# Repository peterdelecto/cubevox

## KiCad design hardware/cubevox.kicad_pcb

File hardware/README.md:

# cubevox hardware

KiCad scaffold cloned from Teensy-H7-Port (read-only source, fxbox commit 48f1e82,
`hardware/fxbox` + `hardware/h7core`). The schematic (`cubevox.kicad_sch` plus the
`h7core_block` child sheet) and the PCB (`cubevox.kicad_pcb`) exist; revision 2 follows
`docs/audits/2026-10-02-schematic-audit.md` (disposition in `...-schematic-audit-response.md`).
Audits, consult packets and reviews all live in `docs/audits/`, dated. The 2026-10-08 order
(a41fe4b) was held for the power switch SWPWR1 and J101 at x 175 (owner 2026-10-09);
`tools/gates.sh` checks the layout, `RUNLOG.md` is the record.

## Contents
1. `cubevox.kicad_sym`, `cubevox.pretty`, `cubevox.3dshapes` - JLC parts from fxbox (20 symbols).
2. `cubevox_h7core.*` - same three for the h7core block (25 symbols, MCU, power, codecs).
3. `sym-lib-table`, `fp-lib-table` - both libs, `${KIPRJMOD}`-relative.
4. `cubevox.json`, `h7core_block.json` - `foreman schematic` specs generated by
   `tools/build_spec.py` from the fxbox sources in `tools/src/`. Edit the generator, not the JSON.
5. `reference/` - fxbox schematics, unmodified, not the cubevox schematic.

## Recipe order (docs/specs/2026-10-02-hardware-design.md)
purpose line, `foreman brief`, PARTS.md with LCSC codes, `foreman schematic` from the
JSON spec, ERC 0 plus visual render, layout. Run `assign_pin_types.py` after any import.

## Tooling
kicad-cli 10.0.5 (/Applications/KiCad/KiCad.app).
Source had no tools/build_spec.py; fxbox.json is hand-kept (fxbox/tools has only routing scripts).
Not copied: .kicad_pcb, .kicad_pro, layout/, jlc_extra/ (holds one SMD tact switch).

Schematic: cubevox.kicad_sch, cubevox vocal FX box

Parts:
C101, C113, C116, C118, C127, C130, C134, C143, C144, C145, C150, C151, C152, C153, C154, C155, C156, C157, C162, C163: 100nF; C0603; LCSC C14663
C111: 2.2uF; C0603; LCSC C23630
C112, C114, C115: 22uF; C1206; LCSC C12891
C117, C135, C137, C138: 10uF; C1206; LCSC C14860
C119, C123: 100pF; C0603; LCSC C14858
C120, C124: 47uF 25V; CAP-SMD_BD6.3-L6.6-W6.6-LS7.6-FD; MPN RVT1E470M0605; LCSC C72521
C121, C125, C139, C141, C160: 10uF 25V; CAP-SMD_BD4.0-L4.3-W4.3-FD; MPN RVT1E100M0405; LCSC C72484
C128, C129, C132: 47pF; C0603; LCSC C1671
C136, C161: 2.2nF; C0603; LCSC C2991172
C142: 10nF; C0603; LCSC C57112
C158: 22uF 25V NP; CAP-SMD_BD6.3-L6.6-W6.6-FD; MPN EEEHP1E220P; LCSC C413679
C159: 100uF 10V; CAP-SMD_BD5.0-L5.3-W5.3-LS6.3-FD; MPN VT1A101M0505; LCSC C191859
C167: 100nF; C_0402_1005Metric; LCSC C1525
C168, C169: 10uF; C_0805_2012Metric; LCSC C15850
D105: SMBJ20CA; SMB_L4.4-W3.6-LS5.4-BI; MPN SMBJ20CA; LCSC C113992
D106: SS34; SMA_L4.3-W2.6-LS5.2-RD; MPN SS34; LCSC C8678
D107, D108: BAT54S; SOT-23_L2.9-W1.3-P1.90-LS2.4-BR; MPN BAT54SLT1G; LCSC C19726
D109, D110: 1N4148W; SOD-123F_L2.7-W1.6-LS3.8-RD; MPN 1N4148W; LCSC C81598
ENC101: EC11E15244B2; SW-TH_EC11E; MPN EC11E15244B2; LCSC C470754
FB101: 120R@100MHz; L_0603_1608Metric; MPN BLM18PG121SN1D; LCSC C14709
FB102: 120R@100MHz; L_0603_1608Metric; LCSC C14709
H101, H102, H103, H104: M3 shell; MountingHole_3.2mm_M3
J101: J_IN NCJ6FA-H; CONN-TH_NCJ6FA-H; MPN NCJ6FA-H; LCSC C368458
J106: DC 9V; DC-IN-TH_PJ-002A; MPN PJ-002A; LCSC C3096082
J108: OUT 6.35mm; AUDIO-TH_PJ-611E_1; MPN PJ-611E; LCSC C309282
J117: OLED SH1106; OLED-1.3-SH1106-I2C-4P; MPN SH1106 1.3in I2C 128x64; LCSC C42379197
K102, K103: G6K-2F-Y DC5; RELAY-SMD_G6K-2F-X-XX; MPN G6K-2F-Y-TR DC5; LCSC C47190
L101: 4.7uH; IND-SMD_L5.0-W5.0_ANR5040T; MPN ANR5040T4R7M; LCSC C7427135
Q101, Q102: MMBT3904; SOT-23-3_L2.9-W1.3-P1.90-LS2.4-BR; MPN MMBT3904; LCSC C20526
R101, R104: 47R; R0603; LCSC C23182
R102, R105: 22k; R0603; LCSC C31850
R103, R106: 1.2k; R0603; LCSC C22765
R108, R110: 4.53k; R0603; LCSC C25971
R109, R126, R150, R159, R160: 1k; R0603; LCSC C21190
R111, R112, R113, R114: 10k 0.1%; R0603; MPN ARG03BTC1002; LCSC C309083
R116, R147: 470R; R0603; LCSC C23179
R117, R118, R120, R122, R127, R128, R129, R134, R135, R136, R137, R138, R139, R140, R141, R151, R152: 10k; R0603; LCSC C25804
R119, R124: 100R; R0603; LCSC C22775
R123: 15k; R0603; LCSC C22809
R125, R144, R145, R148, R149, R153, R161: 100k; R0603; LCSC C25803
R142, R143: 4.7k; R0603; LCSC C23162
R146: 22R; R0603; LCSC C23345
R154, R155: 10k; R_0402_1005Metric; LCSC C25744
R162: 100k; R_0402_1005Metric; LCSC C25741
RV101, RV102, RV103, RV104, RV105, RV106, RV107, RV108, RV109, RV110, RV111, RV112, RV113, RV114, RV115, RV116: 10k; RES-ADJ-TH_RK09D1130C2P; MPN RK09D1130C2P; LCSC C361173
RVGAIN1: 10k GAIN; RES-ADJ-TH_RK09D1130C2P; MPN RK09D1130C2P; LCSC C361173
SW101, SW102, SW103, SW104, SW105, SW106, SW107, SW108: ST-0-102 bat toggle; SW-TH_3P-L8.3-W5.2-P2.54_ST-0-102-A01-T000; MPN ST-0-102-A01-T000-LF; LCSC C1788487
SWBYPASS1: ST-0-102 bat toggle; SW-TH_3P-L8.3-W5.2-P2.54_ST-0-102-A01-T000; MPN ST-0-102-A01-T000-LF; LCSC C1788487
SWPWR1: SS-12D11-G050 power; SW-TH_5P-P4.70_SS-12D11-G050; MPN SS-12D11-G050; LCSC C17179528
TP1: 9V_JACK; TestPoint_Pad_D1.5mm
TP2: VIN_9V; TestPoint_Pad_D1.5mm
TP3: GND; TestPoint_Pad_D1.5mm
TP4: 3V3; TestPoint_Pad_D1.5mm
TP6: 3V3A; TestPoint_Pad_D1.5mm
TP7: 5V; TestPoint_Pad_D1.5mm
TP8: 5VA; TestPoint_Pad_D1.5mm
TP9: 5VA_W; TestPoint_Pad_D1.5mm
TP10: VREF_BUF; TestPoint_Pad_D1.5mm
U101: CD74HC4067; SSOP-24_L8.1-W5.3-P0.65-LS7.8-BL; MPN CD74HC4067SM96; LCSC C98457
U103: AP63205WU-7; TSOT-23-6_L2.9-W1.6-P0.95-LS2.8-BL; MPN AP63205WU-7; LCSC C2071056
U104, U105, U106: OPA2197IDR; SOIC-8_L4.9-W3.9-P1.27-LS6.0-BL; MPN OPA2197IDR; LCSC C139363
U108: OPA197IDBVR; SOT-23-5_L3.0-W1.7-P0.95-LS2.8-BR; LCSC C221351

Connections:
/3V3: J117.2 (VCC), R120.1, R127.1, R128.1, R129.1, R134.1, R135.1, R136.1, R137.1, R138.1, R139.1, R140.1, R141.1, R142.1, R143.1, TP4.1 (1_1); also elsewhere on the board
/3V3A: C101.1, C111.1, RV101.3, RV102.3, RV103.3, RV104.3, RV105.3, RV106.3, RV107.3, RV108.3, RV109.3, RV110.3, RV111.3, RV112.3, RV113.3, RV114.3, RV115.3, RV116.3, TP6.1 (1_1), U101.24 (VCC); also elsewhere on the board
/5V: C114.1, C115.1, D109.1 (K), D110.1 (K), FB101.1, FB102.1, K102.1, K103.1, L101.2, TP7.1 (1_1), U103.1 (FB); also elsewhere on the board
/5VA: C117.1, C118.1, C127.1, C134.1, C167.1, D107.2 (C), D108.2 (C), FB101.2, R117.1, R151.1, TP8.1 (1_1), U104.8 (+VS), U105.8 (+VS), U108.5 (V+); also elsewhere on the board
/5VA_W: C130.1, C168.1, FB102.2, R154.1, TP9.1 (1_1), U106.8 (+VS)
/9V_JACK: D106.2 (A), SWPWR1.1, TP1.1 (1_1)
/9V_PLUG: J106.2, J106.3, SWPWR1.2
/A1_FB: C128.2, C158.1, R108.2, U104.2 (-IN/A)
/A2_FB: C129.2, R109.2, R110.2, U104.6 (-IN/B)
/ADC_RC: C136.1, C137.1, R119.2
/ADC_VINL: C137.2; also elsewhere on the board
/ADC_VINR: C138.1; also elsewhere on the board
/BIAS_W: C169.1, R123.2, R154.2, R155.1, U106.3 (+IN/A)
/BUCK5_BST: C116.1, U103.6 (BST)
/BUCK5_SW: C116.2, L101.1, U103.5 (SW)
/BUF_IN: R122.2, R123.1, U106.5 (+IN/B)
/BUF_OUT: R124.1, U106.6 (-IN/B), U106.7 (OUT/B)
/BUF_R: C141.1, R124.2
/DAC_AC: C139.1, R122.1
/DAC_LP: C139.2, C161.1, R147.2
/DAC_OUTL: R147.1; also elsewhere on the board
/DA_N: R113.2, R114.1, U105.2 (-IN/A)
/DA_P: R111.2, R112.1, U105.3 (+IN/A)
/ENC_MENU_A: C143.1, ENC101.A, R127.2; also elsewhere on the board
/ENC_MENU_B: C144.1, ENC101.B, R128.2; also elsewhere on the board
/ENC_MENU_SW: C145.1, ENC101.D, R129.2; also elsewhere on the board
/G2_BOT: R116.1, RVGAIN1.3
/G2_INV: C132.2, R159.1, RVGAIN1.2, U105.6 (-IN/B)
/G2_RG: C159.1, R116.2, R159.2
/GND: C101.2, C111.2, C112.2, C113.2, C114.2, C115.2, C117.2, C118.2, C119.2, C123.2, C127.2, C130.2, C134.2, C135.2, C136.2, C138.2, C142.2, C143.2, C144.2, C145.2, C150.2, C151.2, C152.2, C153.2, C154.2, C155.2, C156.2, C157.2, C159.2, C160.2, C161.2, C162.2, C163.2, C167.2, C168.2, C169.2, D105.2, D107.1 (A), D108.1 (A), ENC101.C, ENC101.E, ENC101.EH, J101.1, J101.4 (S), J101.8 (G), J106.1, J108.2, J117.1 (GND), K102.7, Q101.2 (E), Q102.2 (E), R118.2, R125.2, R144.2, R145.2, R148.2, R149.2, R152.2, R153.2, R155.2, R161.2, R162.2, RV101.1, RV102.1, RV103.1, RV104.1, RV105.1, RV106.1, RV107.1, RV108.1, RV109.1, RV110.1, RV111.1, RV112.1, RV113.1, RV114.1, RV115.1, RV116.1, SW101.1 (T1), SW102.1 (T1), SW103.1 (T1), SW104.1 (T1), SW105.1 (T1), SW106.1 (T1), SW107.1 (T1), SW108.1 (T1), SWBYPASS1.1 (T1), TP3.1 (1_1), U101.12 (GND), U101.15 (~E), U103.4 (GND), U104.4 (-VS), U105.4 (-VS), U106.4 (-VS), U108.2 (V-); also elsewhere on the board
/I2C_SCL: J117.3 (SCL), R142.2; also elsewhere on the board
/I2C_SDA: J117.4 (SDA), R143.2; also elsewhere on the board
/INA_O1: C128.1, R108.1, R111.1, U104.1 (OUT/A)
/INA_O2: C129.1, R110.1, R113.1, U104.7 (OUT/B)
/IN_N: C124.1, K103.6, R105.2, R106.1, U104.5 (+IN/B)
/IN_P: C120.1, K103.2, R102.2, R103.1, U104.3 (+IN/A)
/LINE_N: C125.1, K103.7, R105.1
/LINE_P: C121.1, K103.3, R102.1
/MIC_N: C123.1, C124.2, D108.3 (A/C), R104.2, R145.1
/MIC_P: C119.1, C120.2, D107.3 (A/C), R101.2, R144.1
/MUTE_BASE: Q101.1 (B), R150.2, R153.1
/MUTE_COIL: D109.2 (A), K102.8, Q101.3 (C)
/MUTE_N: R150.1; also elsewhere on the board
/MUTE_SW: C162.1, R120.2, SWBYPASS1.2 (COM); also elsewhere on the board
/MUX_COM: R126.1, U101.1 (COMMONINOUT/OUTPUT)
/MUX_S0: R162.1, U101.10 (S0); also elsewhere on the board
/MUX_S1: U101.11 (S1); also elsewhere on the board
/MUX_S2: U101.14 (S2); also elsewhere on the board
/MUX_S3: U101.13 (S3); also elsewhere on the board
/OUT_AC: C141.2, K102.3, R125.1
/OUT_TIP: J108.6, K102.4, K102.6
/PAD_BASE: Q102.1 (B), R160.2, R161.1
/PAD_COIL: D110.2 (A), K103.8, Q102.3 (C)
/PAD_EN: R160.1; also elsewhere on the board
/POT01: RV101.2, U101.9 (I0)
/POT02: RV102.2, U101.8 (I1)
/POT03: RV103.2, U101.7 (I2)
/POT04: RV104.2, U101.6 (I3)
/POT05: RV105.2, U101.5 (I4)
/POT06: RV106.2, U101.4 (I5)
/POT07: RV107.2, U101.3 (I6)
/POT08: RV108.2, U101.2 (I7)
/POT09: RV109.2, U101.18 (I13)
/POT10: RV110.2, U101.17 (I14)
/POT11: RV111.2, U101.22 (I9)
/POT12: RV112.2, U101.20 (I11)
/POT13: RV113.2, U101.23 (I8)
/POT14: RV114.2, U101.21 (I10)
/POT15: RV115.2, U101.19 (I12)
/POT16: RV116.2, U101.16 (I15)
/POT_MUX_OUT: C142.1, R126.2; also elsewhere on the board
/PRE1: R114.2, U105.1 (OUT/A), U105.5 (+IN/B)
/PRE_OUT: C132.1, R119.1, RVGAIN1.1, U105.7 (OUT/B)
/RG_MID: C158.2, R109.1
/TOGGLE1: C150.1, R134.2, SW101.2 (COM); also elsewhere on the board
/TOGGLE2: C151.1, R135.2, SW102.2 (COM); also elsewhere on the board
/TOGGLE3: C152.1, R136.2, SW103.2 (COM); also elsewhere on the board
/TOGGLE4: C153.1, R137.2, SW104.2 (COM); also elsewhere on the board
/TOGGLE5: C154.1, R138.2, SW105.2 (COM); also elsewhere on the board
/TOGGLE6: C155.1, R139.2, SW106.2 (COM); also elsewhere on the board
/TOGGLE7: C156.1, R140.2, SW107.2 (COM); also elsewhere on the board
/TOGGLE8: C157.1, R141.2, SW108.2 (COM); also elsewhere on the board
/TRS_R: C125.2, J101.5 (R), R149.1
/TRS_T: C121.2, J101.6 (T), J101.7 (T_SW), R148.1
/U106A_OUT: U106.1 (OUT/A), U106.2 (-IN/A)
/VA_SENSE: C163.1, R151.2, R152.1; also elsewhere on the board
/VIN_9V: C112.1, C113.1, D105.1, D106.1 (K), TP2.1 (1_1), U103.2 (EN), U103.3 (VIN)
/VREF: C160.1, R103.2, R106.2, R112.2, R146.2
/VREF_BUF: R146.1, TP10.1 (1_1), U108.1 (OUT), U108.4 (-IN)
/VREF_DIV: C135.1, R117.2, R118.1, U108.3 (+IN)
/XLR_2: J101.2, R101.1
/XLR_3: J101.3, R104.1

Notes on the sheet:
1. POWER IN
9 V Boss supply, centre pin GND, SS34, TVS, 5 V buck, 5VA rail
5VA analog rail from 5V through FB101
2. MIC / LINE INPUT
XLR leg 47R, BAT54S clamp, 100pF, 100k to GND, 47uF + IN_x. TRS leg 10uF + LINE_x, 22k pad, 100k to GND. 1.2k bias to VREF
Both T holes are the tip (Neutrik: one tip circuit, no switch). No plug detection
3. PREAMP
Stage 1 INA 20.05 dB (U104, U105A). Stage 2 0-29.9 dB on Input Gain pot (U105B)
Chain 20-50 dB XLR / -5.6 to +24.3 dB TRS; DC gain 1 (AC-coupled legs)
RG = R109 1k + C158 22uF bipolar in series, DC gain 1. Gain 1 + 2 x 4.53k / 1k = 10.06
Input Gain pot is the A4 feedback resistor, wiper tied to end 3. G = 1 + Rpot/330
VREF: 5VA divided 10k/10k, 10 uF, follower U106A, 22R into VREF with 10 uF. U106B drives block 6
4. ADC FEED
PRE_OUT always feeds the ADC
VINR unused, AC-coupled to GND
5. MUTE TOGGLE
MUTE_SW low = muted. K102 (section 8) does the muting
Mute toggle. Common to MUTE_SW, one throw to GND, other throw open
6. DAC / OUTPUT
470R / 2.2nF filter, 10uF, BUF_IN = 0.6 x DAC about VREF
U106B buffers to the jack
OUT_TIP via K102 (section 8)
8. OUTPUT MUTE
K102 closes OUT_AC to OUT_TIP when MUTE_N is high, else OUT_TIP is grounded
5VA SENSE
7. PANEL
16 pots to U101 (the mux is full), 1 encoder, 8 toggles, OLED header

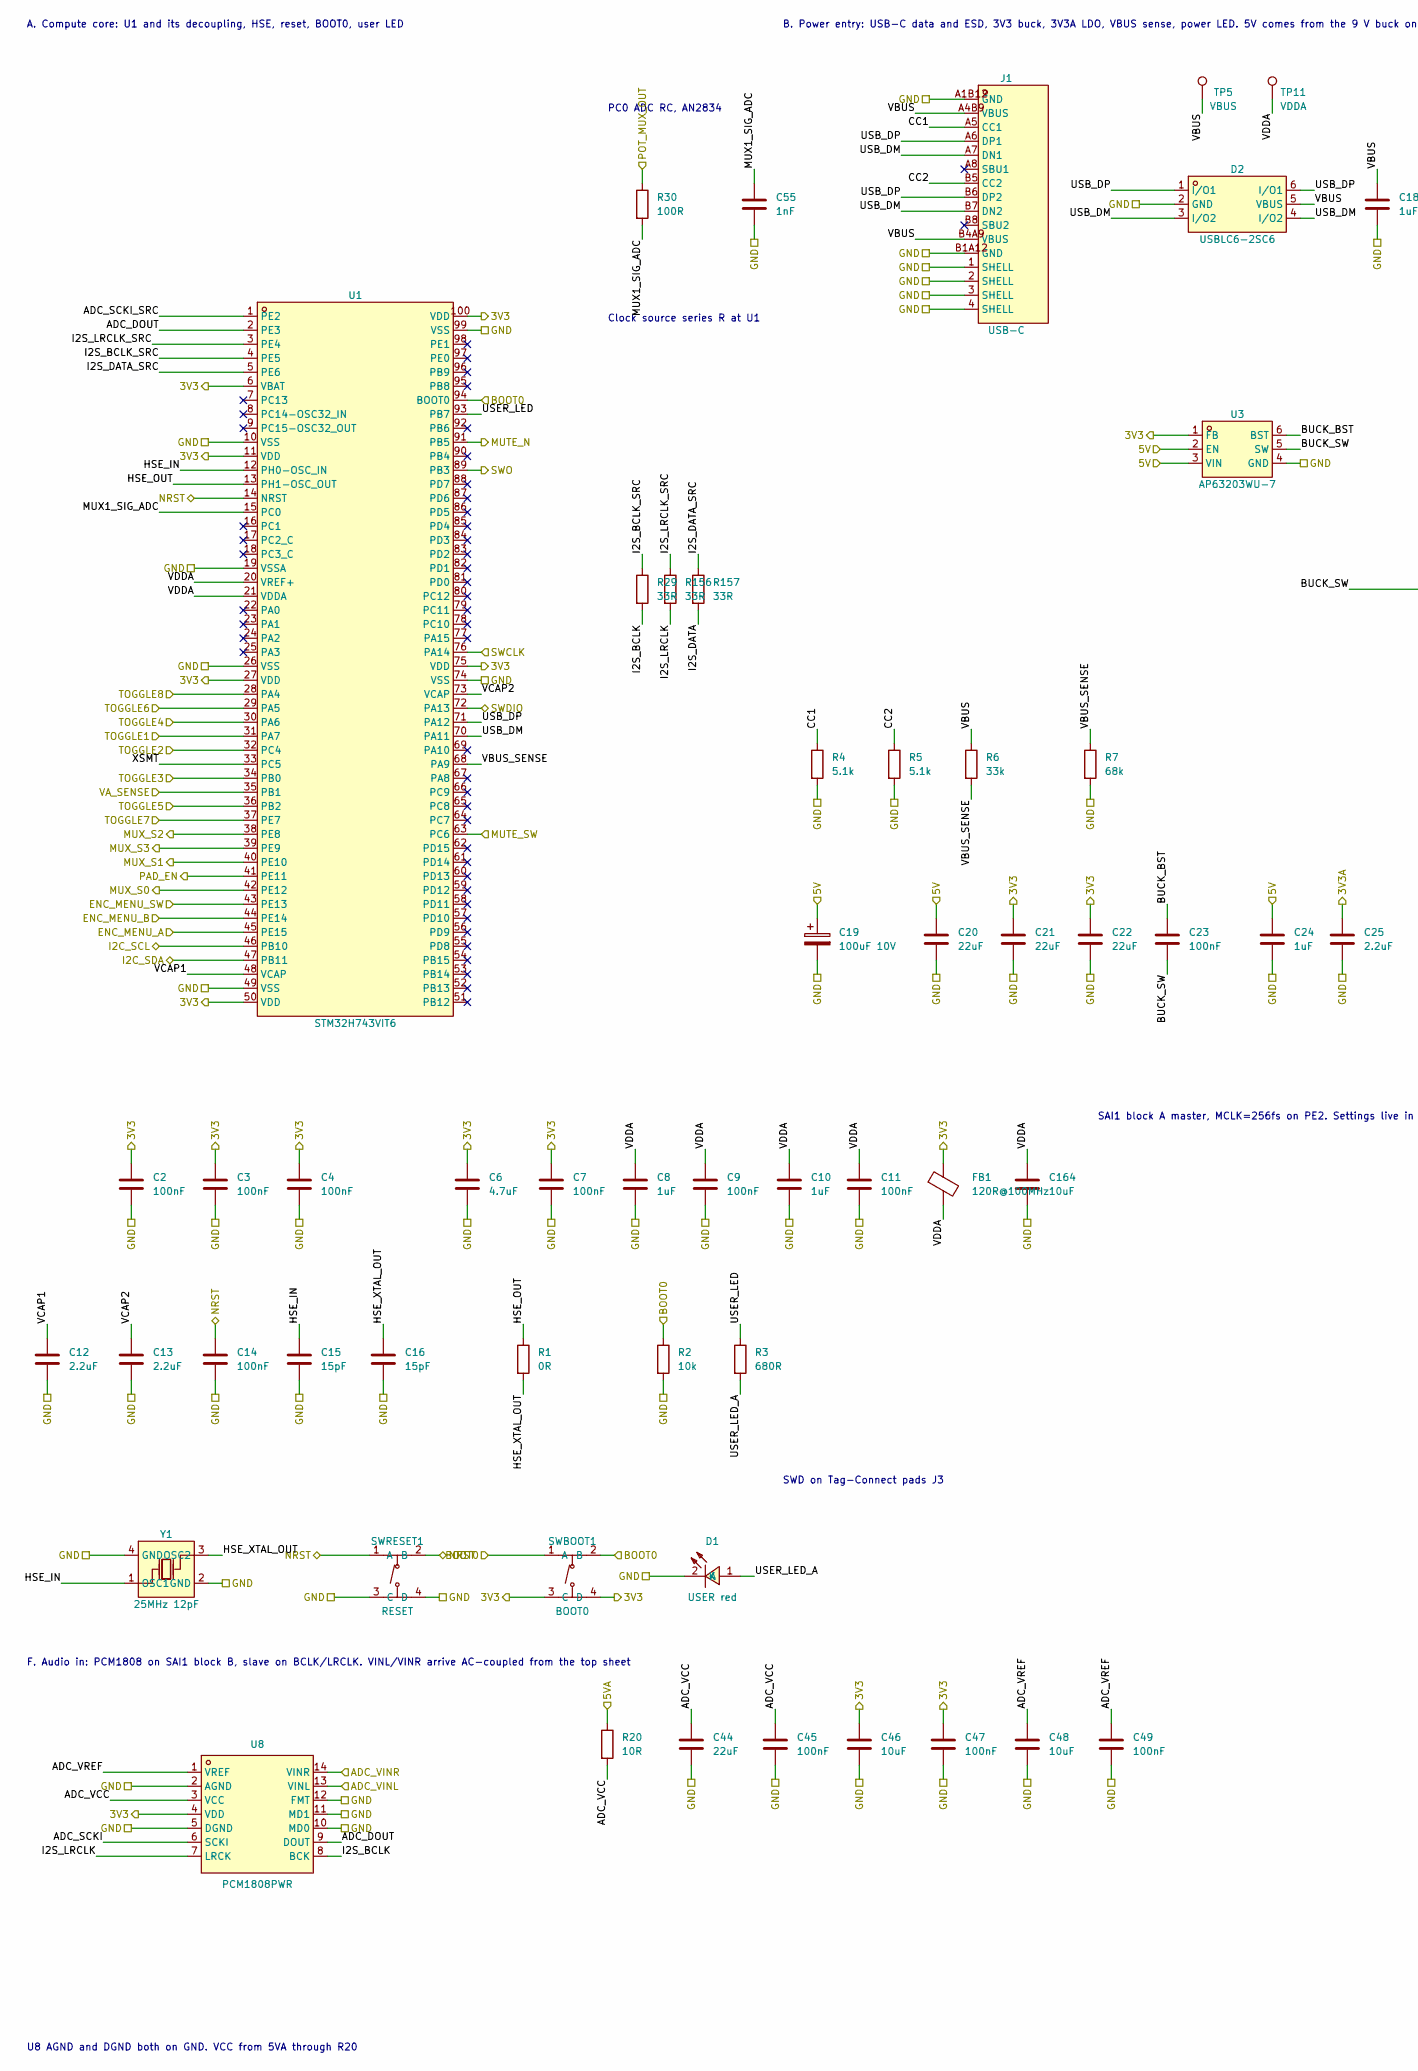
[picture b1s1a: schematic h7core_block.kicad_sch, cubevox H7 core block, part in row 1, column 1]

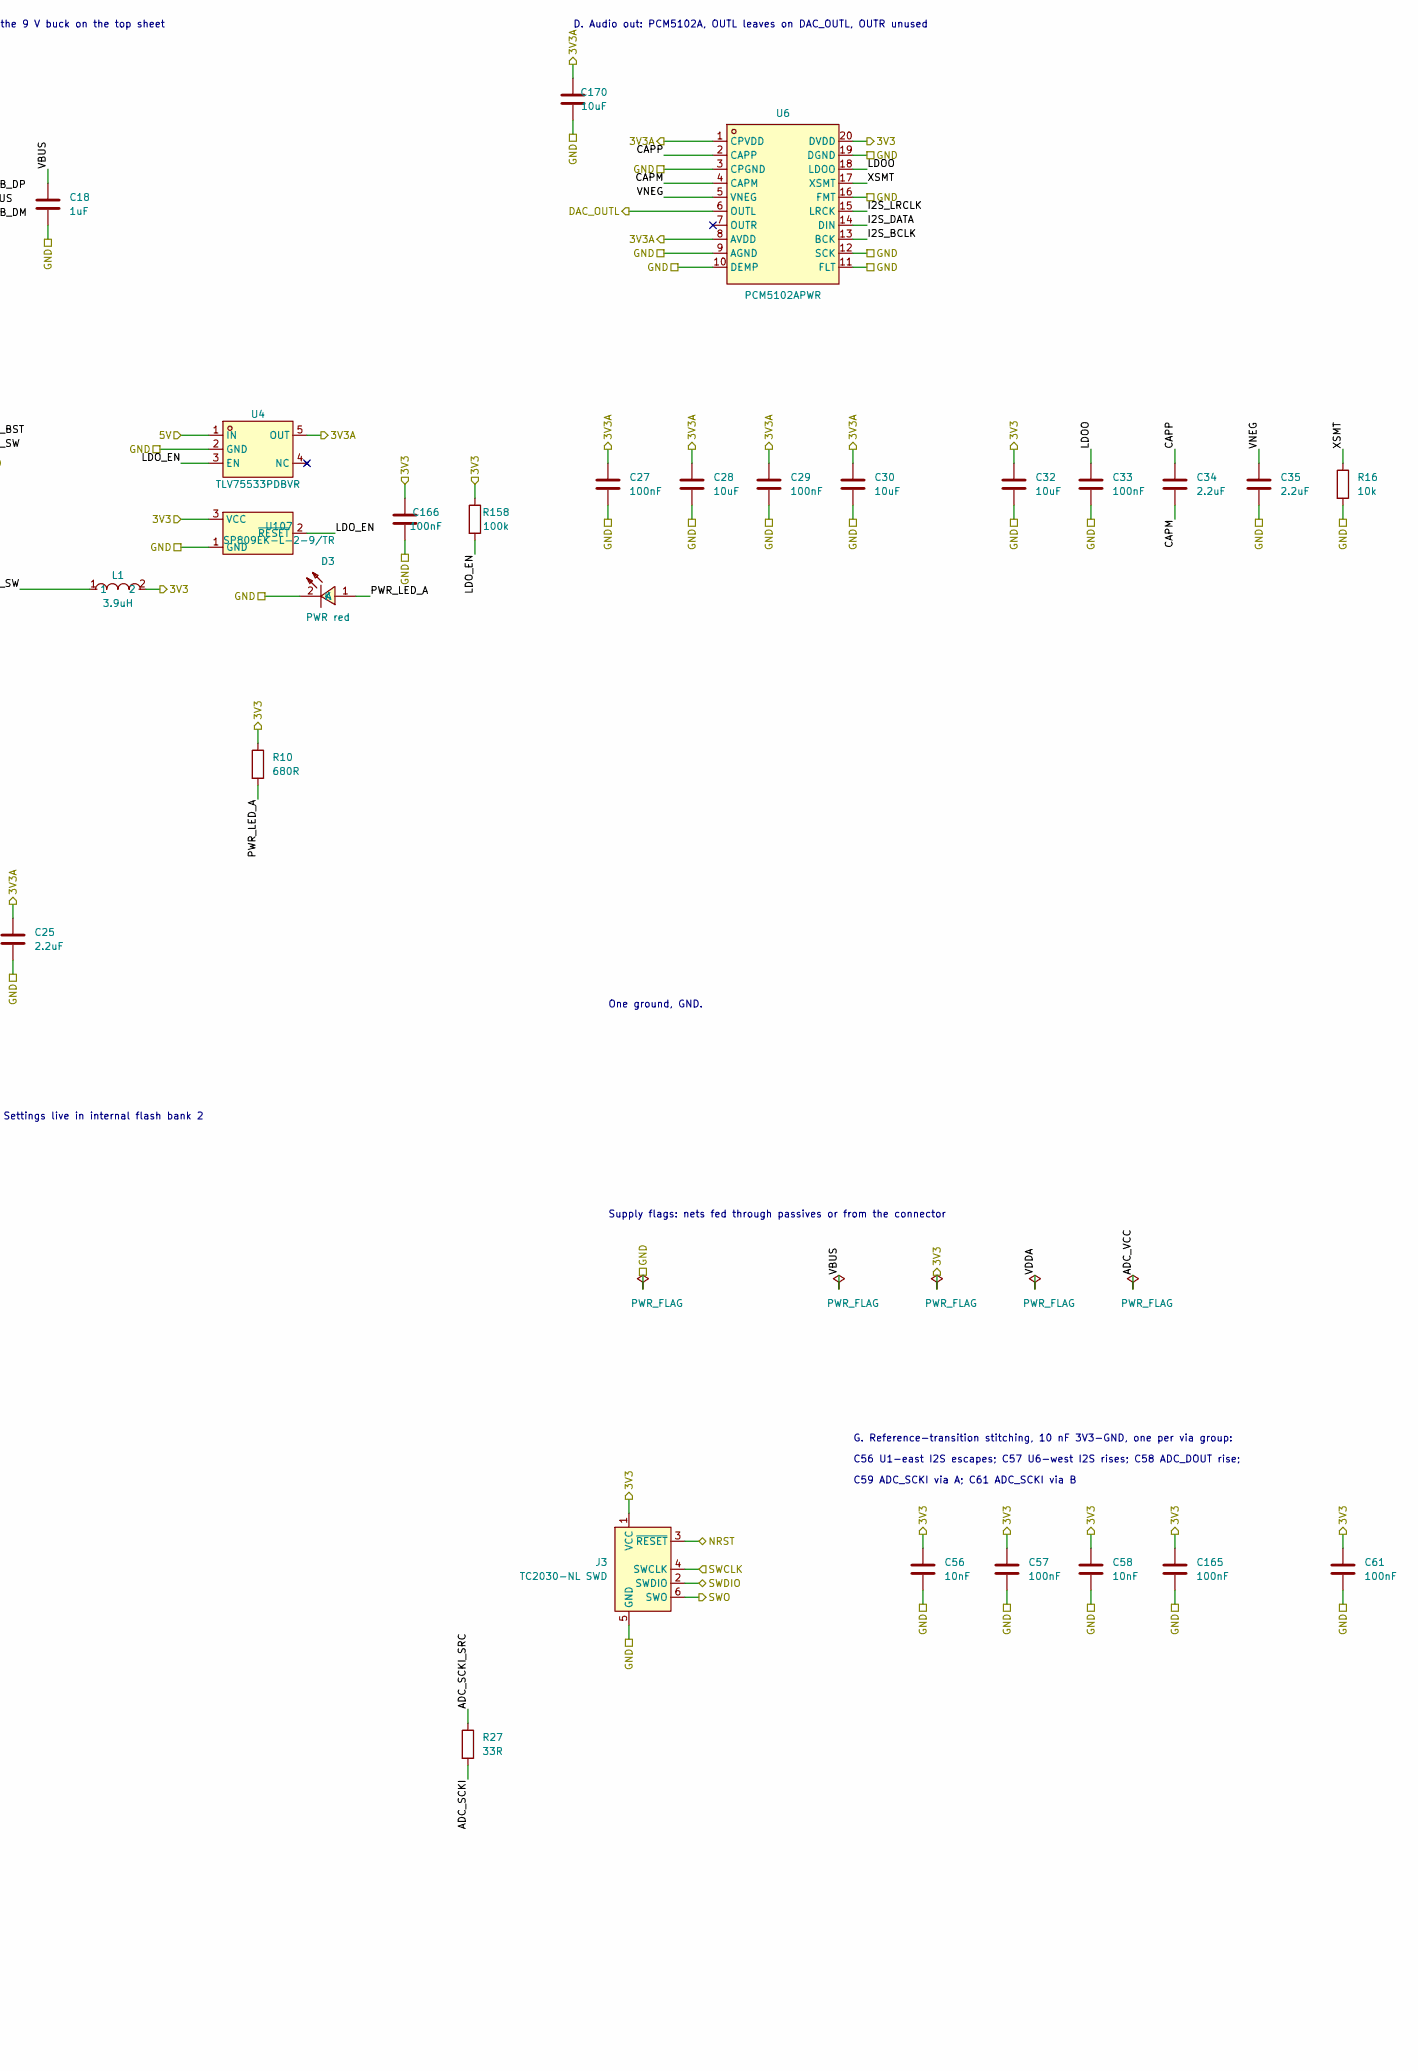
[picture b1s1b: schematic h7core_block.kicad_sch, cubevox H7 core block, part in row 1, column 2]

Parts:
C2, C3, C4, C7, C9, C11, C14, C23, C27, C29, C33, C45, C47, C49: 100nF; C_0603_1608Metric; LCSC C14663
C6: 4.7uF; C_0603_1608Metric; LCSC C19666
C8, C10, C24: 1uF; C_0603_1608Metric; LCSC C15849
C12, C13, C25, C34, C35: 2.2uF; C_0603_1608Metric; LCSC C23630
C15, C16: 15pF; C_0603_1608Metric; LCSC C1644
C18: 1uF; C_0603_1608Metric; LCSC C90540
C19: 100uF 10V; CAP-SMD_L6.0-W3.2-R-RD; LCSC C8649
C20, C21, C22, C44: 22uF; C_1206_3216Metric; LCSC C12891
C28, C30, C32, C46, C48: 10uF; C_0603_1608Metric; LCSC C19702
C55: 1nF; C_0603_1608Metric; LCSC C1588
C56, C58: 10nF; C_0402_1005Metric; LCSC C15195
C57, C61, C165, C166: 100nF; C_0402_1005Metric; LCSC C1525
C164, C170: 10uF; C_0805_2012Metric; LCSC C15850
D1: USER red; LED-SMD_L1.6-W0.8-R-RD; MPN KT-0603R; LCSC C2286
D2: USBLC6-2SC6; SOT-23-6_L2.9-W1.6-P0.95-LS2.8-BL; MPN USBLC6-2SC6; LCSC C2687116
D3: PWR red; LED-SMD_L1.6-W0.8-R-RD; MPN KT-0603R; LCSC C2286
FB1: 120R@100MHz; L_0603_1608Metric; LCSC C14709
J1: USB-C; USB-C-SMD_TYPE-C16PIN; MPN TYPE-C16PIN; LCSC C393939
J3: TC2030-NL SWD; Tag-Connect_TC2030-IDC-NL_2x03_P1.27mm_Vertical
L1: 3.9uH; IND-SMD_L5.0-W5.0; MPN ANR5040T3R9M; LCSC C7427132
R1: 0R; R_0603_1608Metric; LCSC C21189
R2, R16: 10k; R_0603_1608Metric; LCSC C25804
R3, R10: 680R; R_0603_1608Metric; LCSC C23228
R4, R5: 5.1k; R_0603_1608Metric; LCSC C23186
R6: 33k; R_0603_1608Metric; LCSC C4216
R7: 68k; R_0603_1608Metric; LCSC C23231
R20: 10R; R_0603_1608Metric; LCSC C22859
R27, R156, R157: 33R; R_0402_1005Metric; LCSC C25105
R29: 33R; R_0603_1608Metric; LCSC C23140
R30: 100R; R_0603_1608Metric; LCSC C22775
R158: 100k; R_0402_1005Metric; LCSC C25741
SWBOOT1: BOOT0; SW-SMD_4P-L5.1-W5.1-P3.70-LS6.5-TL_H1.5; MPN TS-1187A-B-A-B; LCSC C318884
SWRESET1: RESET; SW-SMD_4P-L5.1-W5.1-P3.70-LS6.5-TL_H1.5; MPN TS-1187A-B-A-B; LCSC C318884
TP5: VBUS; TestPoint_Pad_D1.5mm
TP11: VDDA; TestPoint_Pad_D1.5mm
U1: STM32H743VIT6; LQFP-100_L14.0-W14.0-P0.50-LS16.0-BL; MPN STM32H743VIT6; LCSC C114409
U3: AP63203WU-7; TSOT-26_L2.9-W1.6-P0.95-LS2.8-BL; MPN AP63203WU-7; LCSC C780769
U4: TLV75533PDBVR; SOT-23-5_L3.0-W1.7-P0.95-LS2.8-BR; MPN TLV75533PDBVR; LCSC C404027
U6: PCM5102APWR; TSSOP-20_L6.5-W4.4-P0.65-LS6.4-BL; MPN PCM5102APWR; LCSC C107671
U8: PCM1808PWR; TSSOP-14_L5.0-W4.4-P0.65-LS6.4-BL; MPN PCM1808PWR; LCSC C55513
U107: SP809EK-L-2-9/TR; SOT-23-3_L2.9-W1.6-P1.90-LS2.8-BR; MPN SP809EK-L-2-9/TR; LCSC C412495
Y1: 25MHz 12pF; CRYSTAL-SMD_4P-L3.2-W2.5-BL; MPN X322525MOB4SI; LCSC C9006

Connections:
/3V3: C2.1, C3.1, C4.1, C6.1, C7.1, C21.1, C22.1, C32.1, C46.1, C47.1, C56.1, C57.1, C58.1, C61.1, C165.1, C166.1, FB1.1, J3.1 (VCC), L1.2, R10.1, R158.1, SWBOOT1.3 (C), SWBOOT1.4 (D), U1.6 (VBAT), U1.11 (VDD), U1.27 (VDD), U1.50 (VDD), U1.75 (VDD), U1.100 (VDD), U3.1 (FB), U6.20 (DVDD), U8.4 (VDD), U107.3 (VCC); also elsewhere on the board
/3V3A: C25.1, C27.1, C28.1, C29.1, C30.1, C170.1, U4.5 (OUT), U6.1 (CPVDD), U6.8 (AVDD); also elsewhere on the board
/5V: C19.1, C20.1, C24.1, U3.2 (EN), U3.3 (VIN), U4.1 (IN); also elsewhere on the board
/5VA: R20.1; also elsewhere on the board
/ADC_VINL: U8.13 (VINL); also elsewhere on the board
/ADC_VINR: U8.14 (VINR); also elsewhere on the board
/DAC_OUTL: U6.6 (OUTL); also elsewhere on the board
/ENC_MENU_A: U1.45 (PE15); also elsewhere on the board
/ENC_MENU_B: U1.44 (PE14); also elsewhere on the board
/ENC_MENU_SW: U1.43 (PE13); also elsewhere on the board
/GND: C2.2, C3.2, C4.2, C6.2, C7.2, C8.2, C9.2, C10.2, C11.2, C12.2, C13.2, C14.2, C15.2, C16.2, C18.2, C19.2, C20.2, C21.2, C22.2, C24.2, C25.2, C27.2, C28.2, C29.2, C30.2, C32.2, C33.2, C35.2, C44.2, C45.2, C46.2, C47.2, C48.2, C49.2, C55.2, C56.2, C57.2, C58.2, C61.2, C164.2, C165.2, C166.2, C170.2, D1.2 (K), D2.2 (GND), D3.2 (K), J1.1 (SHELL), J1.2 (SHELL), J1.3 (SHELL), J1.4 (SHELL), J1.A1B12 (GND), J1.B1A12 (GND), J3.5 (GND), R2.2, R4.2, R5.2, R7.2, R16.2, SWRESET1.3 (C), SWRESET1.4 (D), U1.10 (VSS), U1.19 (VSSA), U1.26 (VSS), U1.49 (VSS), U1.74 (VSS), U1.99 (VSS), U3.4 (GND), U4.2 (GND), U6.3 (CPGND), U6.9 (AGND), U6.10 (DEMP), U6.11 (FLT), U6.12 (SCK), U6.16 (FMT), U6.19 (DGND), U8.2 (AGND), U8.5 (DGND), U8.10 (MD0), U8.11 (MD1), U8.12 (FMT), U107.1 (GND), Y1.2 (GND), Y1.4 (GND); also elsewhere on the board
/I2C_SCL: U1.46 (PB10); also elsewhere on the board
/I2C_SDA: U1.47 (PB11); also elsewhere on the board
/MUTE_N: U1.91 (PB5); also elsewhere on the board
/MUTE_SW: U1.63 (PC6); also elsewhere on the board
/MUX_S0: U1.42 (PE12); also elsewhere on the board
/MUX_S1: U1.40 (PE10); also elsewhere on the board
/MUX_S2: U1.38 (PE8); also elsewhere on the board
/MUX_S3: U1.39 (PE9); also elsewhere on the board
/PAD_EN: U1.41 (PE11); also elsewhere on the board
/POT_MUX_OUT: R30.1; also elsewhere on the board
/TOGGLE1: U1.31 (PA7); also elsewhere on the board
/TOGGLE2: U1.32 (PC4); also elsewhere on the board
/TOGGLE3: U1.34 (PB0); also elsewhere on the board
/TOGGLE4: U1.30 (PA6); also elsewhere on the board
/TOGGLE5: U1.36 (PB2); also elsewhere on the board
/TOGGLE6: U1.29 (PA5); also elsewhere on the board
/TOGGLE7: U1.37 (PE7); also elsewhere on the board
/TOGGLE8: U1.28 (PA4); also elsewhere on the board
/VA_SENSE: U1.35 (PB1); also elsewhere on the board
/h7core_block/ADC_DOUT: U1.2 (PE3), U8.9 (DOUT)
/h7core_block/ADC_SCKI: R27.2, U8.6 (SCKI)
/h7core_block/ADC_SCKI_SRC: R27.1, U1.1 (PE2)
/h7core_block/ADC_VCC: C44.1, C45.1, R20.2, U8.3 (VCC)
/h7core_block/ADC_VREF: C48.1, C49.1, U8.1 (VREF)
/h7core_block/BOOT0: R2.1, SWBOOT1.1 (A), SWBOOT1.2 (B), U1.94 (BOOT0)
/h7core_block/BUCK_BST: C23.1, U3.6 (BST)
/h7core_block/BUCK_SW: C23.2, L1.1, U3.5 (SW)
/h7core_block/CAPM: C34.2, U6.4 (CAPM)
/h7core_block/CAPP: C34.1, U6.2 (CAPP)
/h7core_block/CC1: J1.A5 (CC1), R4.1
/h7core_block/CC2: J1.B5 (CC2), R5.1
/h7core_block/HSE_IN: C15.1, U1.12 (PH0-OSC_IN), Y1.1 (OSC1)
/h7core_block/HSE_OUT: R1.1, U1.13 (PH1-OSC_OUT)
/h7core_block/HSE_XTAL_OUT: C16.1, R1.2, Y1.3 (OSC2)
/h7core_block/I2S_BCLK: R29.2, U6.13 (BCK), U8.8 (BCK)
/h7core_block/I2S_BCLK_SRC: R29.1, U1.4 (PE5)
/h7core_block/I2S_DATA: R157.2, U6.14 (DIN)
/h7core_block/I2S_DATA_SRC: R157.1, U1.5 (PE6)
/h7core_block/I2S_LRCLK: R156.2, U6.15 (LRCK), U8.7 (LRCK)
/h7core_block/I2S_LRCLK_SRC: R156.1, U1.3 (PE4)
/h7core_block/LDOO: C33.1, U6.18 (LDOO)
/h7core_block/LDO_EN: R158.2, U4.3 (EN), U107.2 (~RESET)
/h7core_block/MUX1_SIG_ADC: C55.1, R30.2, U1.15 (PC0)
/h7core_block/NRST: C14.1, J3.3 (~RESET), SWRESET1.1 (A), SWRESET1.2 (B), U1.14 (NRST)
/h7core_block/PWR_LED_A: D3.1 (A), R10.2
/h7core_block/SWCLK: J3.4 (SWCLK), U1.76 (PA14)
/h7core_block/SWDIO: J3.2 (SWDIO), U1.72 (PA13)
/h7core_block/SWO: J3.6 (SWO), U1.89 (PB3)
/h7core_block/USB_DM: D2.3 (I/O2), D2.4 (I/O2), J1.A7 (DN1), J1.B7 (DN2), U1.70 (PA11)
/h7core_block/USB_DP: D2.1 (I/O1), D2.6 (I/O1), J1.A6 (DP1), J1.B6 (DP2), U1.71 (PA12)
/h7core_block/USER_LED: R3.1, U1.93 (PB7)
/h7core_block/USER_LED_A: D1.1 (A), R3.2
/h7core_block/VBUS: C18.1, D2.5 (VBUS), J1.A4B9 (VBUS), J1.B4A9 (VBUS), R6.1, TP5.1 (1_1)
/h7core_block/VBUS_SENSE: R6.2, R7.1, U1.68 (PA9)
/h7core_block/VCAP1: C12.1, U1.48 (VCAP)
/h7core_block/VCAP2: C13.1, U1.73 (VCAP)
/h7core_block/VDDA: C8.1, C9.1, C10.1, C11.1, C164.1, FB1.2, TP11.1 (1_1), U1.20 (VREF+), U1.21 (VDDA)
/h7core_block/VNEG: C35.1, U6.5 (VNEG)
/h7core_block/XSMT: R16.1, U1.33 (PC5), U6.17 (XSMT)

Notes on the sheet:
A. Compute core: U1 and its decoupling, HSE, reset, BOOT0, user LED
B. Power entry: USB-C data and ESD, 3V3 buck, 3V3A LDO, VBUS sense, power LED. 5V comes from the 9 V buck on the top sheet
D. Audio out: PCM5102A, OUTL leaves on DAC_OUTL, OUTR unused
One ground, GND.
SAI1 block A master, MCLK=256fs on PE2. Settings live in internal flash bank 2
SWD on Tag-Connect pads J3
Supply flags: nets fed through passives or from the connector
F. Audio in: PCM1808 on SAI1 block B, slave on BCLK/LRCLK. VINL/VINR arrive AC-coupled from the top sheet
U8 AGND and DGND both on GND. VCC from 5VA through R20
PC0 ADC RC, AN2834
Clock source series R at U1
G. Reference-transition stitching, 10 nF 3V3-GND, one per via group:
C56 U1-east I2S escapes; C57 U6-west I2S rises; C58 ADC_DOUT rise;
C59 ADC_SCKI via A; C61 ADC_SCKI via B
